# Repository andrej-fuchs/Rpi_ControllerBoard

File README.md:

I/O Controller Board for Raspberry Pi Zero W2

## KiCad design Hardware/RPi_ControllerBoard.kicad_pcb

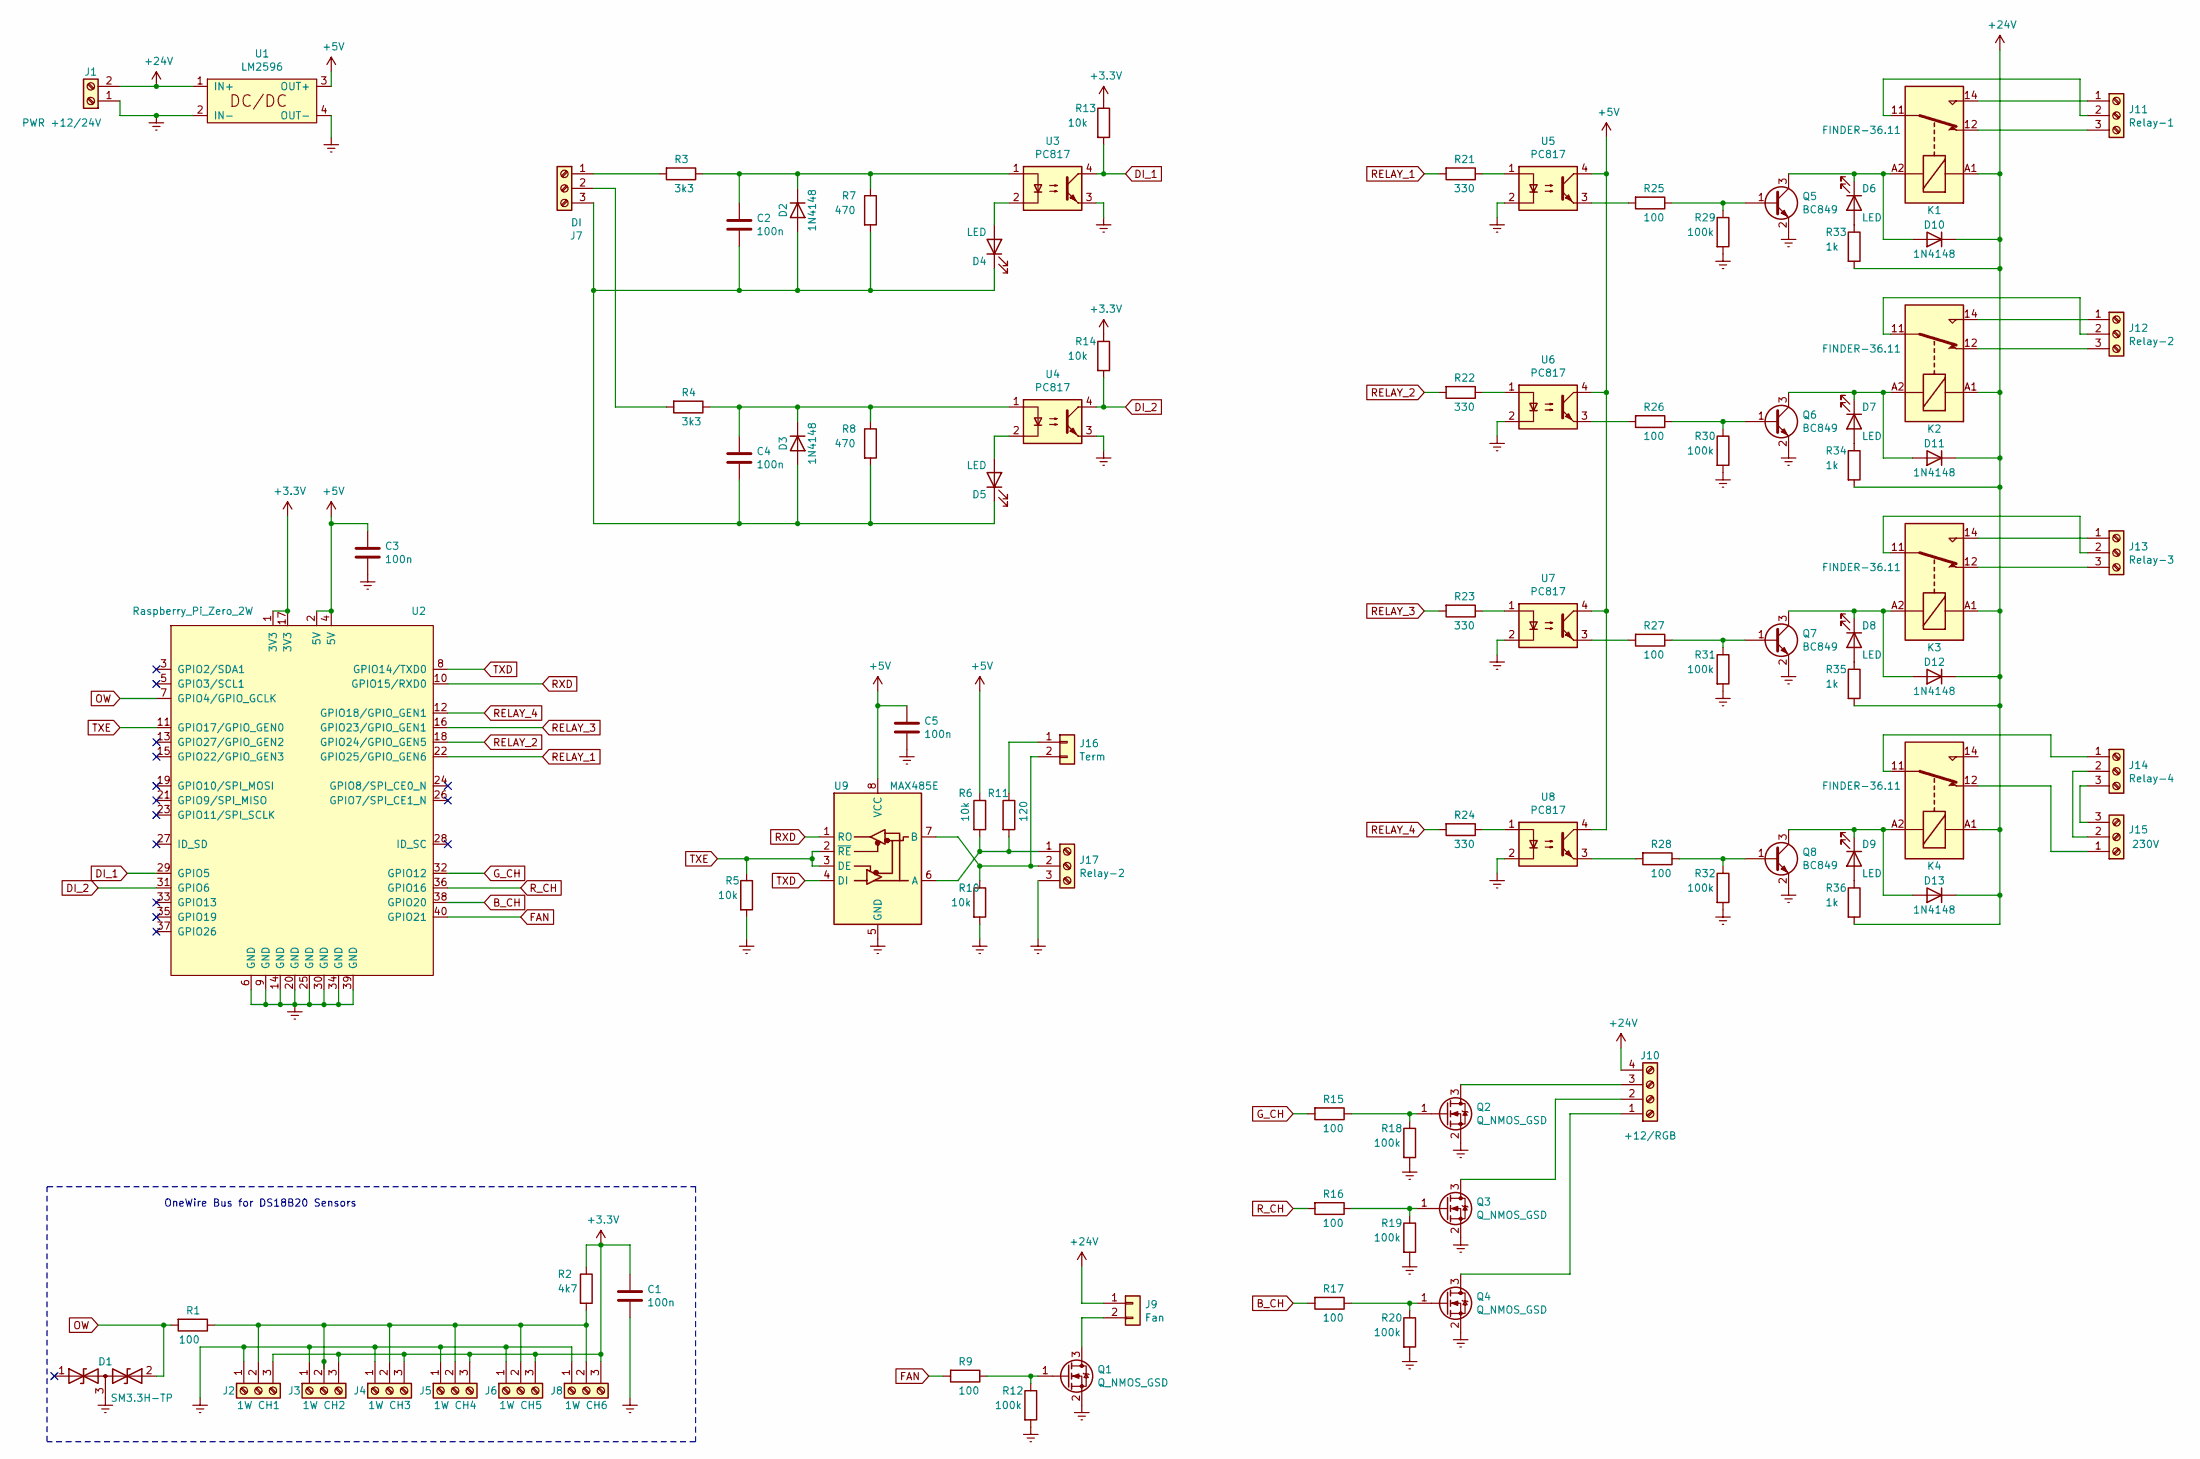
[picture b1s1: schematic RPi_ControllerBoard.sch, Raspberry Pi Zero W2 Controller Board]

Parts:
C1, C2, C3, C4, C5: 100n; C_0805_2012Metric
D1: SM3.3H-TP; SOT-23
D2, D3, D10, D11, D12, D13: 1N4148; D_DO-35_SOD27_P7.62mm_Horizontal
D4, D5, D6, D7, D8, D9: LED; LED_1206_3216Metric
J1: PWR +12/24V; TerminalBlock_Phoenix_MKDS-1,5-2-5.08_1x02_P5.08mm_Horizont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
J2: 1W CH1; TerminalBlock_MetzConnect_Type059_RT06303HBWC_1x03_P3.50mm_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
J3: 1W CH2; TerminalBlock_MetzConnect_Type059_RT06303HBWC_1x03_P3.50mm_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
J4: 1W CH3; TerminalBlock_MetzConnect_Type059_RT06303HBWC_1x03_P3.50mm_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
J5: 1W CH4; TerminalBlock_MetzConnect_Type059_RT06303HBWC_1x03_P3.50mm_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
J6: 1W CH5; TerminalBlock_MetzConnect_Type059_RT06303HBWC_1x03_P3.50mm_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
J7: DI; TerminalBlock_Phoenix_MKDS-1,5-3-5.08_1x03_P5.08mm_Horizont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
J8: 1W CH6; TerminalBlock_MetzConnect_Type059_RT06303HBWC_1x03_P3.50mm_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
J9: Fan; PinHeader_1x02_P2.54mm_Vertical
J10: +12/RGB; TerminalBlock_MetzConnect_Type059_RT06304HBWC_1x04_P3.50mm_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
J11: Relay-1; TerminalBlock_Phoenix_MKDS-1,5-3-5.08_1x03_P5.08mm_Horizont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
J12, J17: Relay-2; TerminalBlock_Phoenix_MKDS-1,5-3-5.08_1x03_P5.08mm_Horizont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
J13: Relay-3; TerminalBlock_Phoenix_MKDS-1,5-3-5.08_1x03_P5.08mm_Horizont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
J14: Relay-4; TerminalBlock_Phoenix_MKDS-1,5-3-5.08_1x03_P5.08mm_Horizont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
J15: 230V; TerminalBlock_Phoenix_MKDS-1,5-3-5.08_1x03_P5.08mm_Horizont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
J16: Term; PinHeader_1x02_P2.54mm_Vertical
K1, K2, K3, K4: FINDER-36.11; Relay_SPDT_Finder_36.11
Q1, Q2, Q3, Q4: Q_NMOS_GSD; SOT-23
Q5, Q6, Q7, Q8: BC849; SOT-23
R1, R9, R15, R16, R17, R25, R26, R27, R28: 100; R_0805_2012Metric
R2: 4k7; R_0805_2012Metric
R3, R4: 3k3; R_0805_2012Metric
R5, R6, R10, R13, R14: 10k; R_0805_2012Metric
R7, R8: 470; R_0805_2012Metric
R11: 120; R_1206_3216Metric
R12, R18, R19, R20, R29, R30, R31, R32: 100k; R_0805_2012Metric
R21, R22, R23, R24: 330; R_0805_2012Metric
R33, R34, R35, R36: 1k; R_0805_2012Metric
U1: LM2596; LM2596S-DC-DC
U2: Raspberry_Pi_Zero_2W; RaspberryPi-Zero-2W
U3, U4, U5, U6, U7, U8: PC817; DIP-4_W7.62mm
U9: MAX485E; DIP-8_W7.62mm_LongPads

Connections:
+3V3: C1.2, J2.3, J3.3, J4.3, J5.3, J6.3, J8.3, R2.1, R13.1, R14.1, U2.1 (3V3), U2.17 (3V3)
+5V: C3.2, C5.2, R6.1, U1.3 (OUT+), U2.2 (5V), U2.4 (5V), U5.4, U6.4, U7.4, U8.4, U9.8 (VCC)
+24V: D10.1 (K), D11.1 (K), D12.1 (K), D13.1 (K), J1.2, J9.1, J10.4, K1.A1, K2.A1, K3.A1, K4.A1, R33.2, R34.2, R35.2, R36.2, U1.1 (IN+)
B_CH: R17.2, U2.38 (GPIO20)
DI_1: R13.2, U2.29 (GPIO5), U3.4
DI_2: R14.2, U2.31 (GPIO6), U4.4
Earth: C1.1, C3.1, C5.1, D1.3 (common), J1.1, J2.1, J3.1, J4.1, J5.1, J6.1, J8.1, J17.3, Q1.2 (S), Q2.2 (S), Q3.2 (S), Q4.2 (S), Q5.2 (E), Q6.2 (E), Q7.2 (E), Q8.2 (E), R5.2, R10.2, R12.2, R18.2, R19.2, R20.2, R29.2, R30.2, R31.2, R32.2, U1.2 (IN-), U1.4 (OUT-), U2.6 (GND), U2.9 (GND), U2.14 (GND), U2.20 (GND), U2.25 (GND), U2.30 (GND), U2.34 (GND), U2.39 (GND), U3.3, U4.3, U5.2, U6.2, U7.2, U8.2, U9.5 (GND)
FAN: R9.2, U2.40 (GPIO21)
G_CH: R15.2, U2.32 (GPIO12)
unnamed: C2.1, C4.1, D2.2 (A), D3.2 (A), D4.1 (K), D5.1 (K), J7.3, R7.2, R8.2
unnamed: C2.2, D2.1 (K), R3.1, R7.1, U3.1
unnamed: C4.2, D3.1 (K), R4.1, R8.1, U4.1
unnamed: D4.2 (A), U3.2
unnamed: D5.2 (A), U4.2
unnamed: D6.2 (A), R33.1
unnamed: D7.2 (A), R34.1
unnamed: D8.2 (A), R35.1
unnamed: D9.2 (A), R36.1
unnamed: D6.1 (K), D10.2 (A), K1.A2, Q5.3 (C)
unnamed: D7.1 (K), D11.2 (A), K2.A2, Q6.3 (C)
unnamed: D8.1 (K), D12.2 (A), K3.A2, Q7.3 (C)
unnamed: D9.1 (K), D13.2 (A), K4.A2, Q8.3 (C)
unnamed: J2.2, J3.2, J4.2, J5.2, J6.2, J8.2, R1.1, R2.2
unnamed: J7.1, R3.2
unnamed: J7.2, R4.2
unnamed: J9.2, Q1.3 (D)
unnamed: J10.1, Q4.3 (D)
unnamed: J10.2, Q3.3 (D)
unnamed: J10.3, Q2.3 (D)
unnamed: J11.1, K1.14
unnamed: J11.2, K1.11
unnamed: J11.3, K1.12
unnamed: J12.1, K2.14
unnamed: J12.2, K2.11
unnamed: J12.3, K2.12
unnamed: J13.1, K3.14
unnamed: J13.2, K3.11
unnamed: J13.3, K3.12
unnamed: J14.1, K4.11
unnamed: J14.2, J15.2
unnamed: J14.3, J15.3
unnamed: J15.1, K4.12
unnamed: J16.1, R11.1
unnamed: J16.2, J17.2, R10.1, U9.7 (B)
unnamed: J17.1, R6.2, R11.2, U9.6 (A)
unnamed: Q1.1 (G), R9.1, R12.1
unnamed: Q2.1 (G), R15.1, R18.1
unnamed: Q3.1 (G), R16.1, R19.1
unnamed: Q4.1 (G), R17.1, R20.1
unnamed: Q5.1 (B), R25.1, R29.1
unnamed: Q6.1 (B), R26.1, R30.1
unnamed: Q7.1 (B), R27.1, R31.1
unnamed: Q8.1 (B), R28.1, R32.1
unnamed: R21.1, U5.1
unnamed: R22.1, U6.1
unnamed: R23.1, U7.1
unnamed: R24.1, U8.1
unnamed: R25.2, U5.3
unnamed: R26.2, U6.3
unnamed: R27.2, U7.3
unnamed: R28.2, U8.3
OW: D1.2 (A2), R1.2, U2.7 (GPIO4/GPIO_GCLK)
RELAY_1: R21.2, U2.22 (GPIO25/GPIO_GEN6)
RELAY_2: R22.2, U2.18 (GPIO24/GPIO_GEN5)
RELAY_3: R23.2, U2.16 (GPIO23/GPIO_GEN1)
RELAY_4: R24.2, U2.12 (GPIO18/GPIO_GEN1)
RXD: U2.10 (GPIO15/RXD0), U9.1 (RO)
R_CH: R16.2, U2.36 (GPIO16)
TXD: U2.8 (GPIO14/TXD0), U9.4 (DI)
TXE: R5.1, U2.11 (GPIO17/GPIO_GEN0), U9.2 (~RE), U9.3 (DE)

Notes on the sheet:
OneWire Bus for DS18B20 Sensors

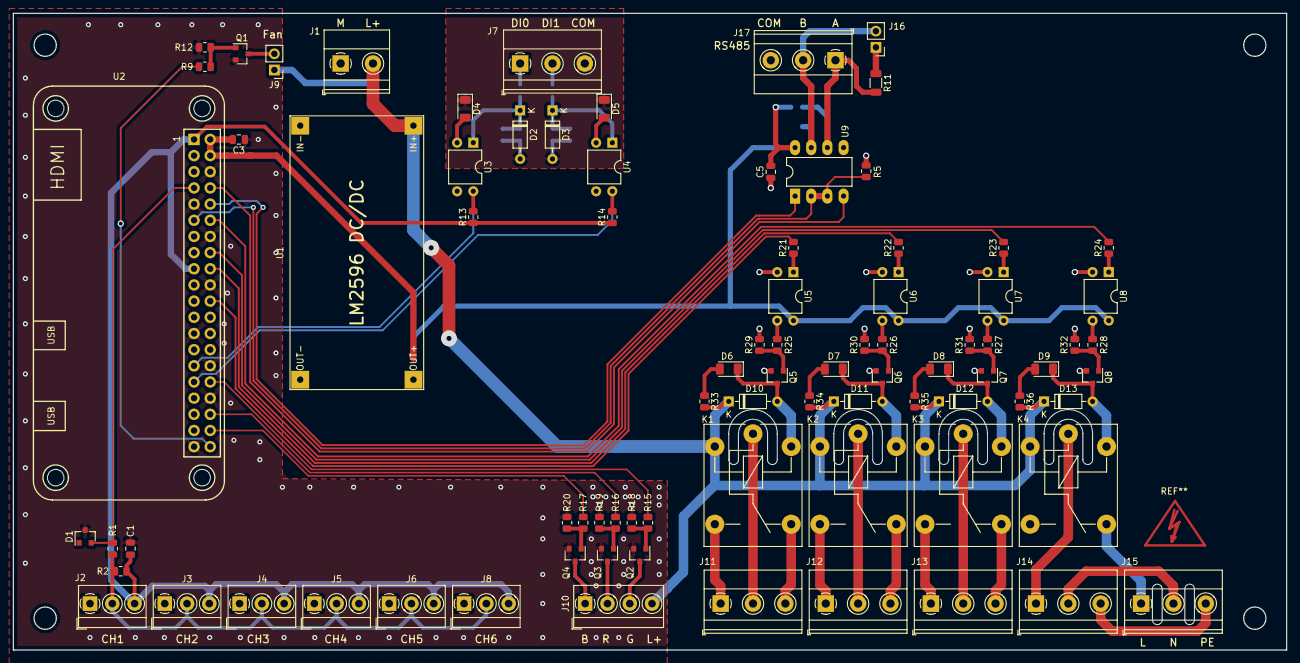
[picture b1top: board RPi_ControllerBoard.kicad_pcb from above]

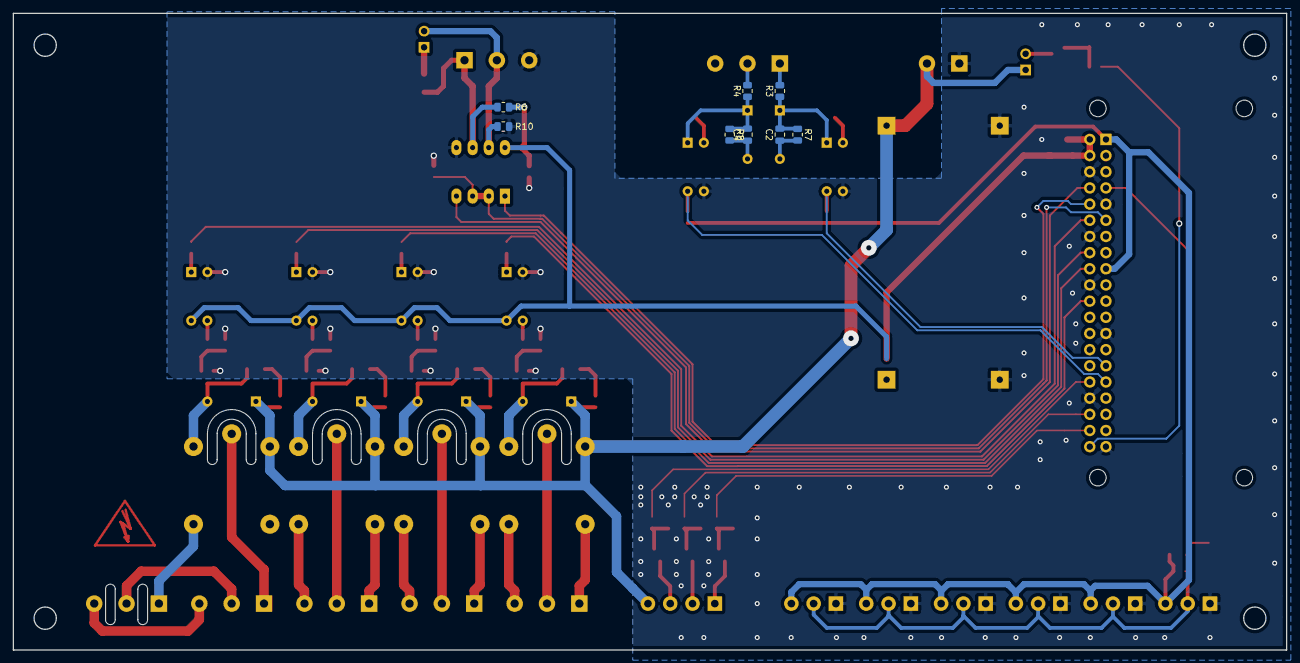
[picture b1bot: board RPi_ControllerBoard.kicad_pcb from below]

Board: 2 copper layers, 200.0 x 100.0 mm, 92 parts (8 on the bottom side), 70 nets.

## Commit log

2021-11-08 Initial Commit / Add Schematic
2021-11-14 add pcb layout
